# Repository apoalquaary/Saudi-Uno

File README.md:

<h1>Saudi UNO PCB Project</h1>
<p>This repository hosts the PCB design files for the Saudi UNO, an Arduino UNO-compatible device designed in the shape of the Saudi map. It's intended primarily for educational use in electronics and microcontroller programming.</p>

<h2>Project Overview</h2>
<p>The Saudi UNO is a unique Arduino UNO variant, customized to reflect the geographic outline of Saudi Arabia. It serves as an educational tool to engage students in learning about electronics design and practical PCB layout techniques.</p>

<h2>Files Included</h2>
<ul>
    <li><strong>Gerber Files:</strong> Contains all necessary manufacturing data for the PCB.</li>
    <li><strong>Schematic Files:</strong> Electronic schematics detailing component placement and connections.</li>
    <li><strong>Assembly Drawings:</strong> Helpful for visualizing component placement during the soldering process.</li>
    <li><strong>Bill of Materials (BOM):</strong> A comprehensive list of all components required to build the Saudi UNO.</li>
</ul>

<image src="https://github.com/apoalquaary/Saudi-Uno/blob/main/images/photo_5908730412442698918_y.jpg">
<image src="https://github.com/apoalquaary/Saudi-Uno/blob/main/images/photo_5908730412442698917_y.jpg">
<image src="https://github.com/apoalquaary/Saudi-Uno/blob/main/images/photo_5908730412442698921_y.jpg">
<image src="https://github.com/apoalquaary/Saudi-Uno/blob/main/images/photo_5908730412442698924_y.jpg">
<image src="https://github.com/apoalquaary/Saudi-Uno/blob/main/images/photo_5908730412442698913_y.jpg">

<h2>How to Use</h2>
<p>To use these files:</p>
<ol>
    <li>Download the desired files from the repository.</li>
    <li>Contact a PCB manufacturer and provide them with the Gerber files for production.</li>
    <li>Refer to the assembly drawings and BOM for assembling the PCB once manufactured.</li>
</ol>

<h2>Prerequisites</h2>
<p>You will need access to PCB manufacturing services and basic soldering tools to assemble the board. Familiarity with electronic components and soldering is recommended.</p>

<h2>Contributing</h2>
<p>If you have suggestions for improving the design, or have developed a variant of the Saudi UNO, please consider submitting a pull request. See <code>CONTRIBUTING.md</code> for more details on how to contribute.</p>

<h2>License</h2>
<p>This project is distributed under the Saudi UNO Non-Commercial License, which allows for non-commercial use such as academic and personal learning free of charge. Commercial use requires prior approval. For complete terms, see the <code>LICENSE</code> file.</p>

<h2>Contact</h2>
<p>For inquiries about commercial use or further questions, please reach out via [Your Email Address].</p>

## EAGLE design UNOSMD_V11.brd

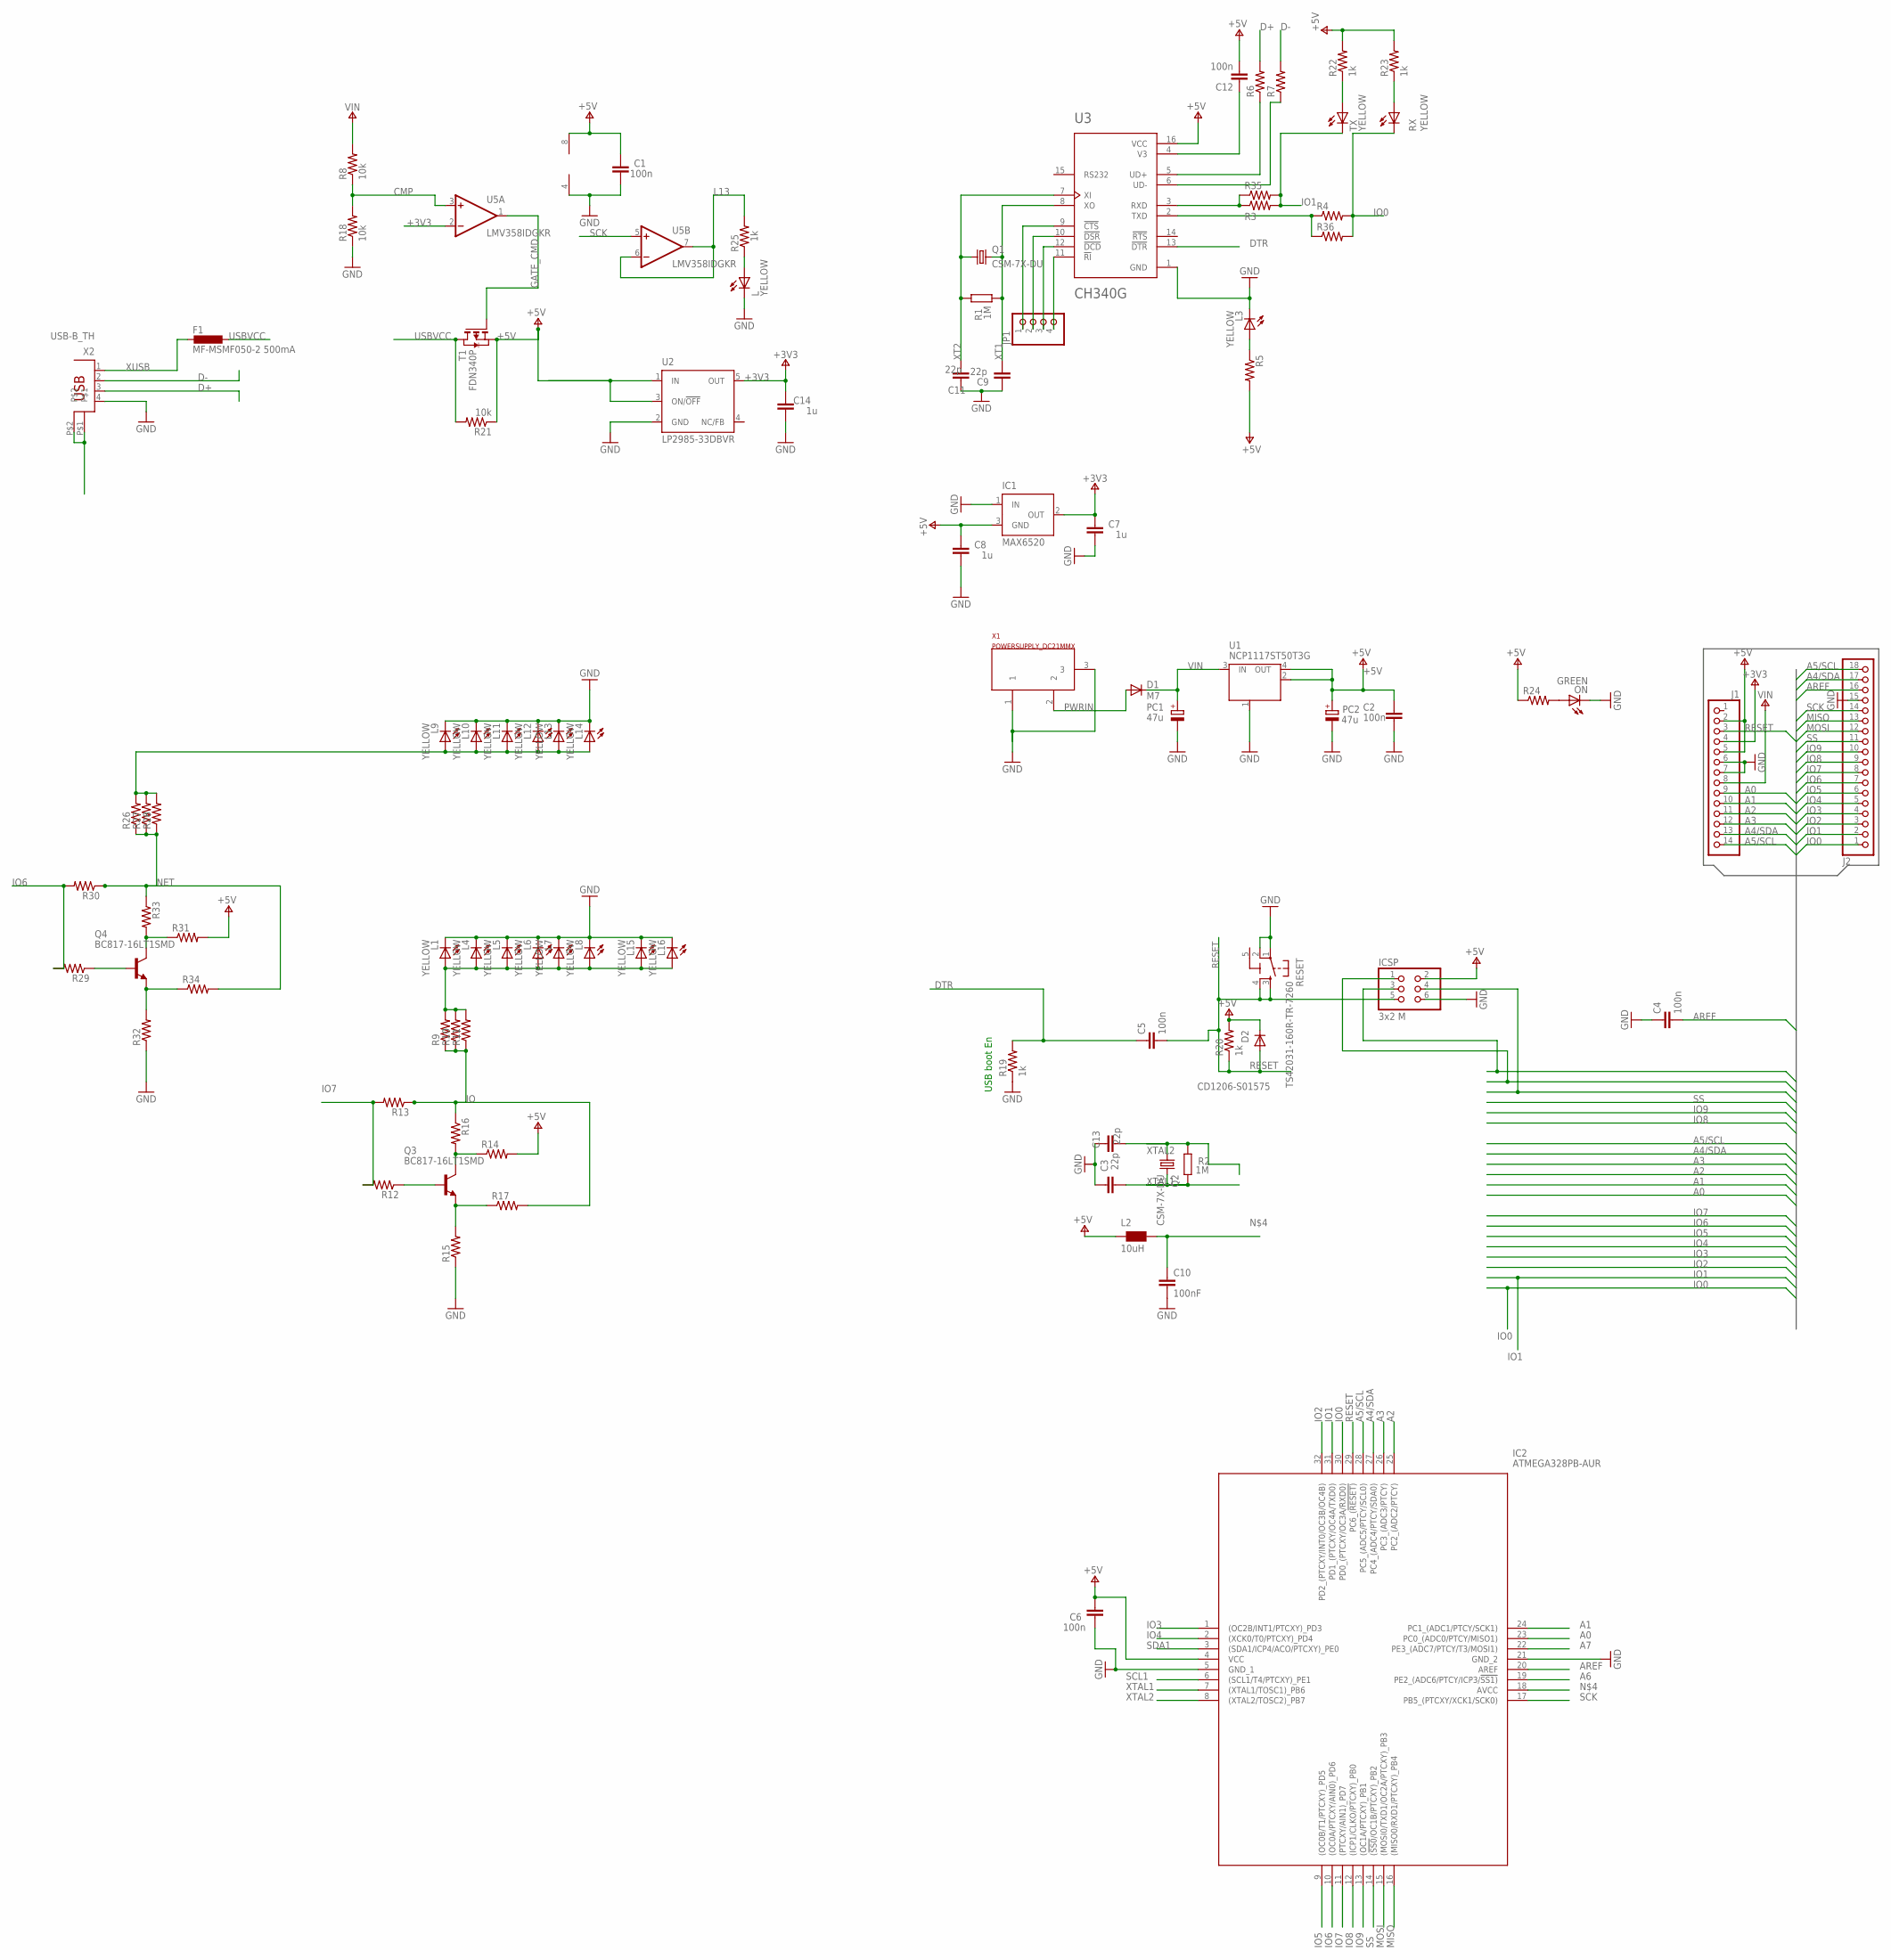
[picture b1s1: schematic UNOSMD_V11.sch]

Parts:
C1, C2, C4, C5, C6, C12: 100n; C0603-ROUND
C3, C9, C11, C13: 22p; C0603-ROUND
C7, C8, C14: 1u; C0603-ROUND
C10: 100nF; C0603-ROUND
D1: M7; SMB
D2: CD1206-S01575; MINIMELF
F1: MF-MSMF050-2 500mA; L1812
IC1: MAX6520; SOT23
IC2: ATMEGA328PB-AUR; QFP80P900X900X120-32N
ICSP: 3x2 M; 2X03
J1: -; 1X14-CUSTOM
J2: -; 1X18-CUSTOM
JP1: PINHD-1X4; 1X04
L, L1, L3, L4, L5, L6, L7, L8, L9, L10, L11, L12, L13, L14, L15, L16: YELLOW; CHIP-LED0805
L2: 10uH; 0805
ON: GREEN; CHIP-LED0805
PC1, PC2: 47u; PANASONIC_D
Q1, Q2: CSM-7X-DU
Q3, Q4: BC817-16LT1SMD; SOT23-BEC
R1, R2: 1M; R0603-ROUND
R3, R4, R5, R6, R7, R9, R10, R11, R12, R13, R14, R15, R16, R17, R24, R26, R27, R28, R29, R30, R31, R32, R33, R34, R35, R36: R-US_R0603; R0603
R8, R18, R21: 10k; R0603
R19, R20, R22, R23, R25: 1k; R0603
RESET: TS42031-160R-TR-7260; TS42
RX: YELLOW; CHIP-LED0805
T1: FDN340P; SOT-23
TX: YELLOW; CHIP-LED0805
U1: NCP1117ST50T3G; SOT223
U2: LP2985-33DBVR; SOT23-DBV
U3: CH340G; SOIC127P600X180-16N
U5: LMV358IDGKR; MSOP08
X1: POWERSUPPLY_DC21MMX; POWERSUPPLY_DC-21MM
X2: USB-B_TH; PN61729

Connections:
5-GND: RESET.5 (5-GND)
+3V3: C7.2, C14.2, IC1.2 (OUT), J1.4, U2.5 (OUT), U5.2 (-IN)
+5V: C1.2, C2.2, C6.2, C8.2, C12.2, D2.C, IC1.3 (GND), IC2.4 (VCC), ICSP.2, J1.2, J1.5, L2.1, PC2.+, R5.2, R14.2, R20.2, R21.1, R22.2, R23.2, R24.1, R31.2, T1.2 (S), U1.2 (OUT), U1.4 (OUT), U2.1 (IN), U2.3 (ON/!OFF), U3.16 (VCC), U5.8 (V+)
A0: IC2.23 (PC0_(ADC0/PTCY/MISO1)), J1.9
A1: IC2.24 (PC1_(ADC1/PTCY/SCK1)), J1.10
A2: IC2.25 (PC2_(ADC2/PTCY)), J1.11
A3: IC2.26 (PC3_(ADC3/PTCY)), J1.12
A4/SDA: IC2.27 (PC4_(ADC4/PTCY/SDA0)), J1.13, J2.17
A5/SCL: IC2.28 (PC5_(ADC5/PTCY/SCL0)), J1.14, J2.18
A6: IC2.19 (PE2_(ADC6/PTCY/ICP3/!SS1))
A7: IC2.22 (PE3_(ADC7/PTCY/T3/MOSI1))
AREF: C4.2, IC2.20 (AREF), J2.16
CMP: R8.1, R18.2, U5.3 (+IN)
D+: R6.2, X2.3
D-: R7.2, X2.2
DTR: C5.1, R19.2, U3.13 (!DTR)
GATE_CMD: T1.3 (G), U5.1 (OUT)
GND: C1.1, C2.1, C3.2, C4.1, C6.1, C7.1, C8.1, C9.2, C10.2, C11.2, C13.2, C14.1, IC1.1 (IN), IC2.5 (GND_1), IC2.21 (GND_2), ICSP.6, J1.6, J1.7, J2.15, L.C, L1.C, L3.C, L4.C, L5.C, L6.C, L7.C, L8.C, L9.C, L10.C, L11.C, L12.C, L13.C, L14.C, L15.C, L16.C, ON.C, PC1.-, PC2.-, R15.1, R18.1, R19.1, R32.1, RESET.1, RESET.2, U1.1 (GND/ADJ), U2.2 (GND), U3.1 (GND), U5.4 (V-), X1.1, X1.3, X2.4
IO: R9.1, R10.1, R11.1, R13.1, R16.1, R17.2
IO0: IC2.30 (PD0_(PTCXY/OC3A/RXD0)), J2.1, R4.2, R36.2, RX.C
IO1: IC2.31 (PD1_(PTCXY/OC4A/TXD0)), J2.2, R3.2, R35.2, TX.C
IO2: IC2.32 (PD2_(PTCXY/INT0/OC3B/OC4B)), J2.3
IO3: IC2.1 ((OC2B/INT1/PTCXY)_PD3), J2.4
IO4: IC2.2 ((XCK0/T0/PTCXY)_PD4), J2.5
IO5: IC2.9 ((OC0B/T1/PTCXY)_PD5), J2.6
IO6: IC2.10 ((OC0A/PTCXY/AIN0)_PD6), J2.7, R29.2, R30.2
IO7: IC2.11 ((PTCXY/AIN1)_PD7), J2.8, R12.2, R13.2
IO8: IC2.12 ((ICP1/CLKO/PTCXY)_PB0), J2.9
IO9: IC2.13 ((OC1A/PTCXY)_PB1), J2.10
L13: R25.2, U5.6 (-IN), U5.7 (OUT)
MISO: IC2.16 ((MISO0/RXD1/PTCXY)_PB4), ICSP.1, J2.13
MOSI: IC2.15 ((MOSI0/TXD1/OC2A/PTCXY)_PB3), ICSP.4, J2.12
unnamed: ON.A, R24.2
unnamed: R3.1, R35.1, U3.3 (RXD)
unnamed: C10.1, IC2.18 (AVCC), L2.2
unnamed: R4.1, R36.1, U3.2 (TXD)
unnamed: C12.1, U3.4 (V3)
unnamed: L3.A, R5.1
unnamed: R6.1, U3.5 (UD+)
unnamed: R7.1, U3.6 (UD-)
unnamed: L.A, R25.1
unnamed: Q3.B, R12.1
unnamed: JP1.1, U3.9 (!CTS)
unnamed: Q3.E, R15.2, R17.1
unnamed: Q3.C, R14.1, R16.2
unnamed: JP1.2, U3.10 (!DSR)
unnamed: JP1.3, U3.12 (!DCD)
unnamed: JP1.4, U3.11 (!RI)
unnamed: L1.A, L4.A, L5.A, L6.A, L7.A, L8.A, L15.A, L16.A, R9.2, R10.2, R11.2
unnamed: Q4.B, R29.1
unnamed: Q4.E, R32.2, R34.1
unnamed: Q4.C, R31.1, R33.2
unnamed: L9.A, L10.A, L11.A, L12.A, L13.A, L14.A, R26.2, R27.2, R28.2
unnamed: R23.1, RX.A
unnamed: R22.1, TX.A
NET: R26.1, R27.1, R28.1, R30.1, R33.1, R34.2
PWRIN: D1.A, X1.2
RESET: C5.2, D2.A, IC2.29 (PC6_(!RESET)), ICSP.5, J1.3, R20.1, RESET.3, RESET.4
SCK: IC2.17 (PB5_(PTCXY/XCK1/SCK0)), ICSP.3, J2.14, U5.5 (+IN)
SCL1: IC2.6 ((SCL1/T4/PTCXY)_PE1)
SDA1: IC2.3 ((SDA1/ICP4/ACO/PTCXY)_PE0)
SS: IC2.14 ((!SS0!/OC1B/PTCXY)_PB2), J2.11
USBVCC: F1.1, R21.2, T1.1 (D)
USHIELD: X2.P$1, X2.P$2
VIN: D1.C, J1.8, PC1.+, R8.2, U1.3 (IN)
XT1: C9.1, Q1.2, R1.1, U3.8 (XO)
XT2: C11.1, Q1.1, R1.2, U3.7 (XI)
XTAL1: C3.1, IC2.7 ((XTAL1/TOSC1)_PB6), Q2.2, R2.1
XTAL2: C13.1, IC2.8 ((XTAL2/TOSC2)_PB7), Q2.1, R2.2
XUSB: F1.2, X2.1

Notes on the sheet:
USB boot En

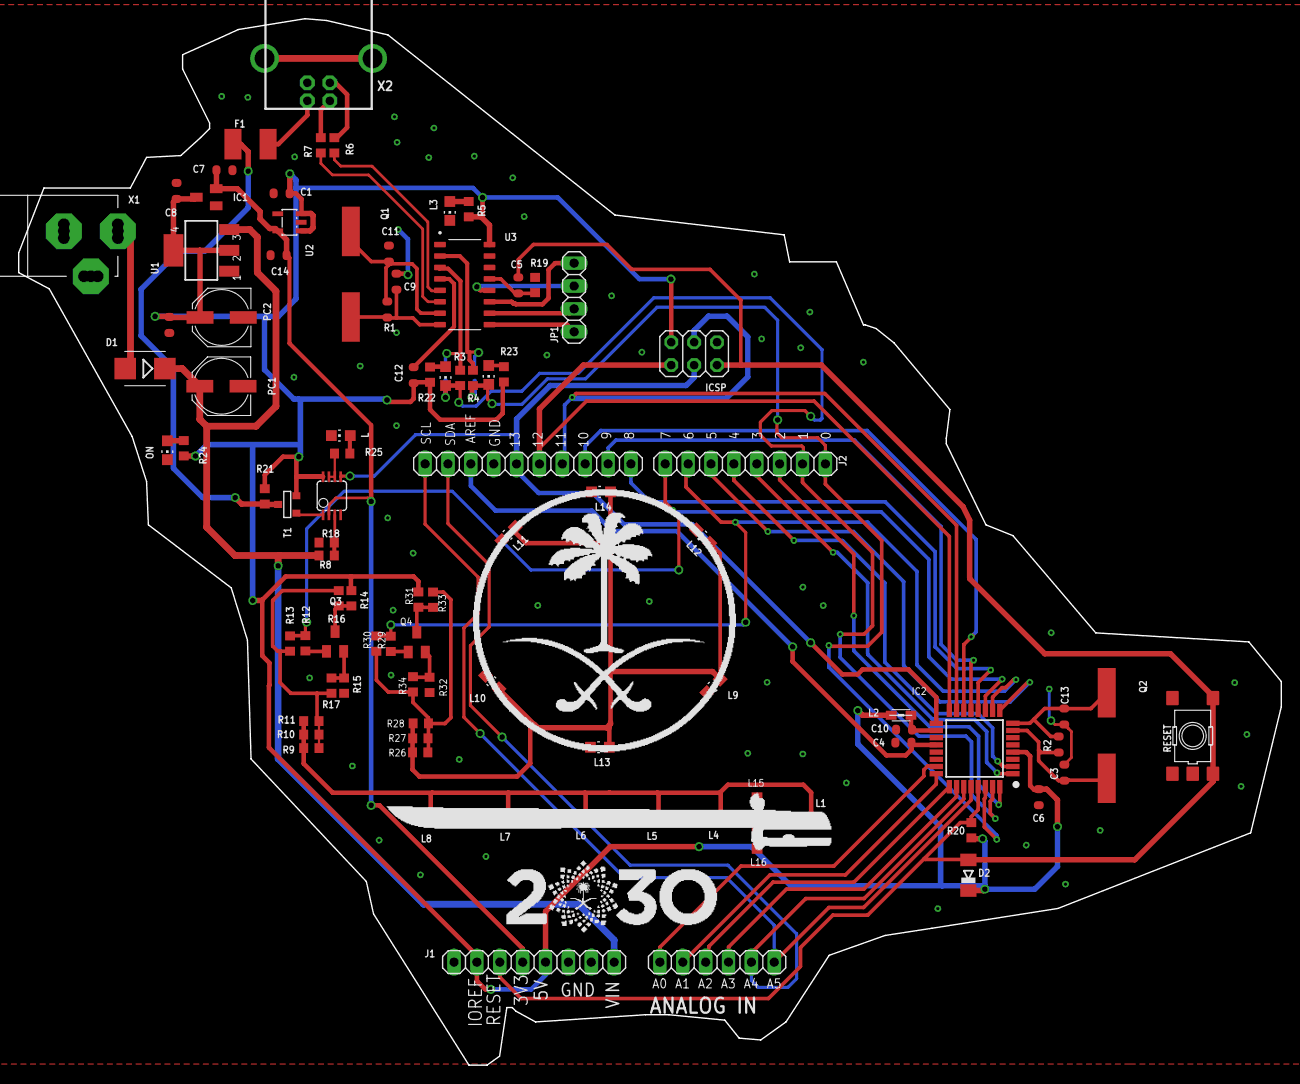
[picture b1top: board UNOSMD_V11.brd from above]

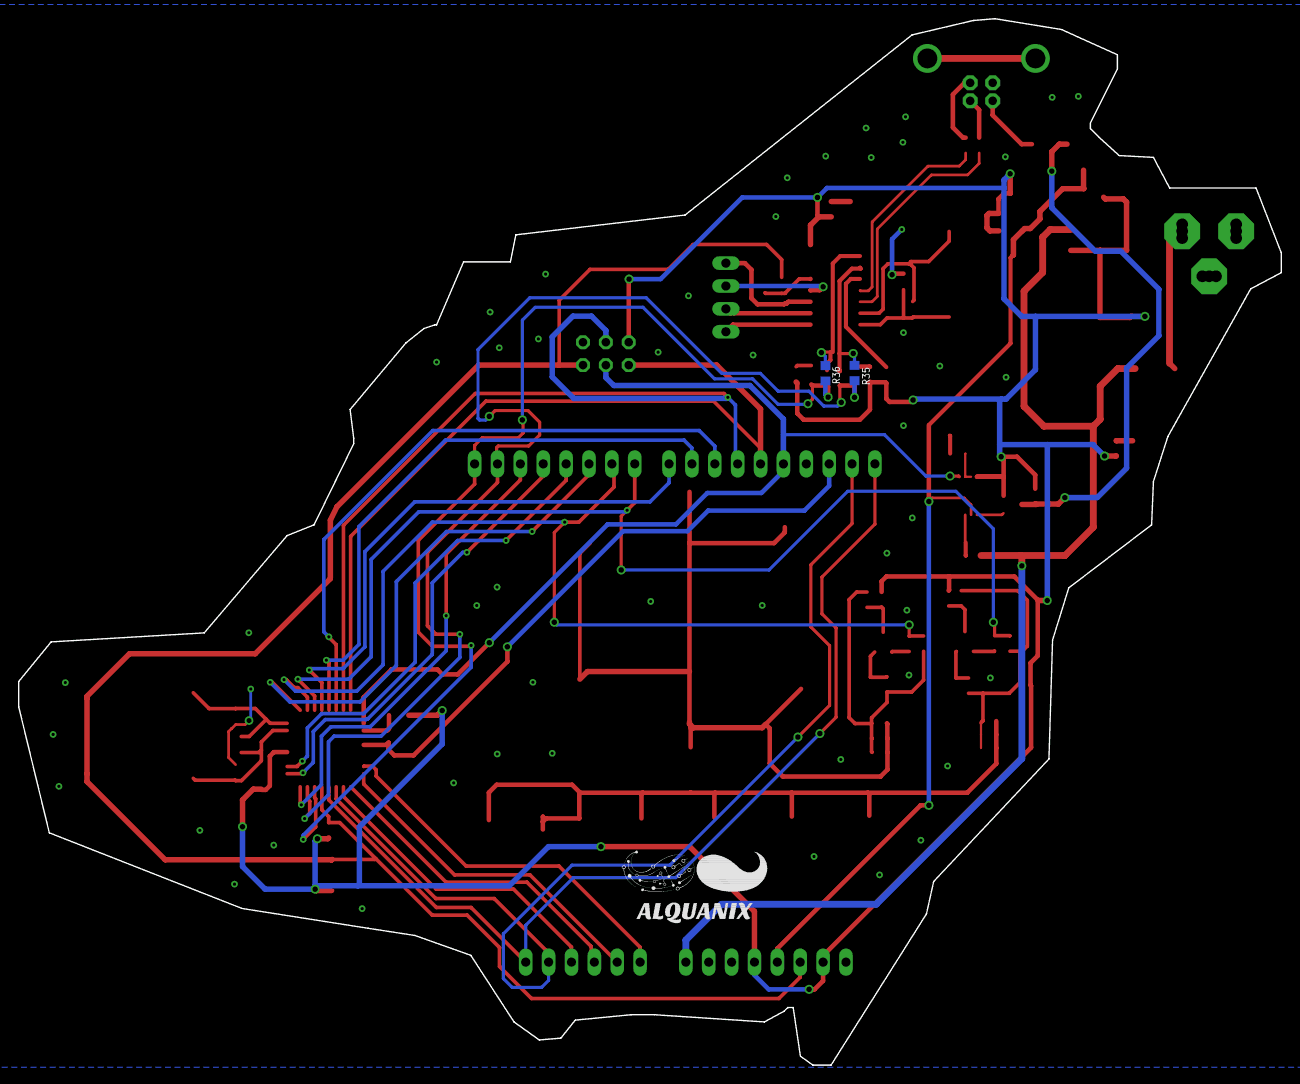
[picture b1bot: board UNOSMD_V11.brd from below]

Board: 2 copper layers, 140.2 x 116.2 mm, 93 parts (2 on the bottom side), 65 nets.

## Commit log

2024-08-16 Initializing

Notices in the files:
parts and their libraries:
Arduino-connectors: Copyright (c) 2016-2017 Arduino LLC.  All right reserved.
